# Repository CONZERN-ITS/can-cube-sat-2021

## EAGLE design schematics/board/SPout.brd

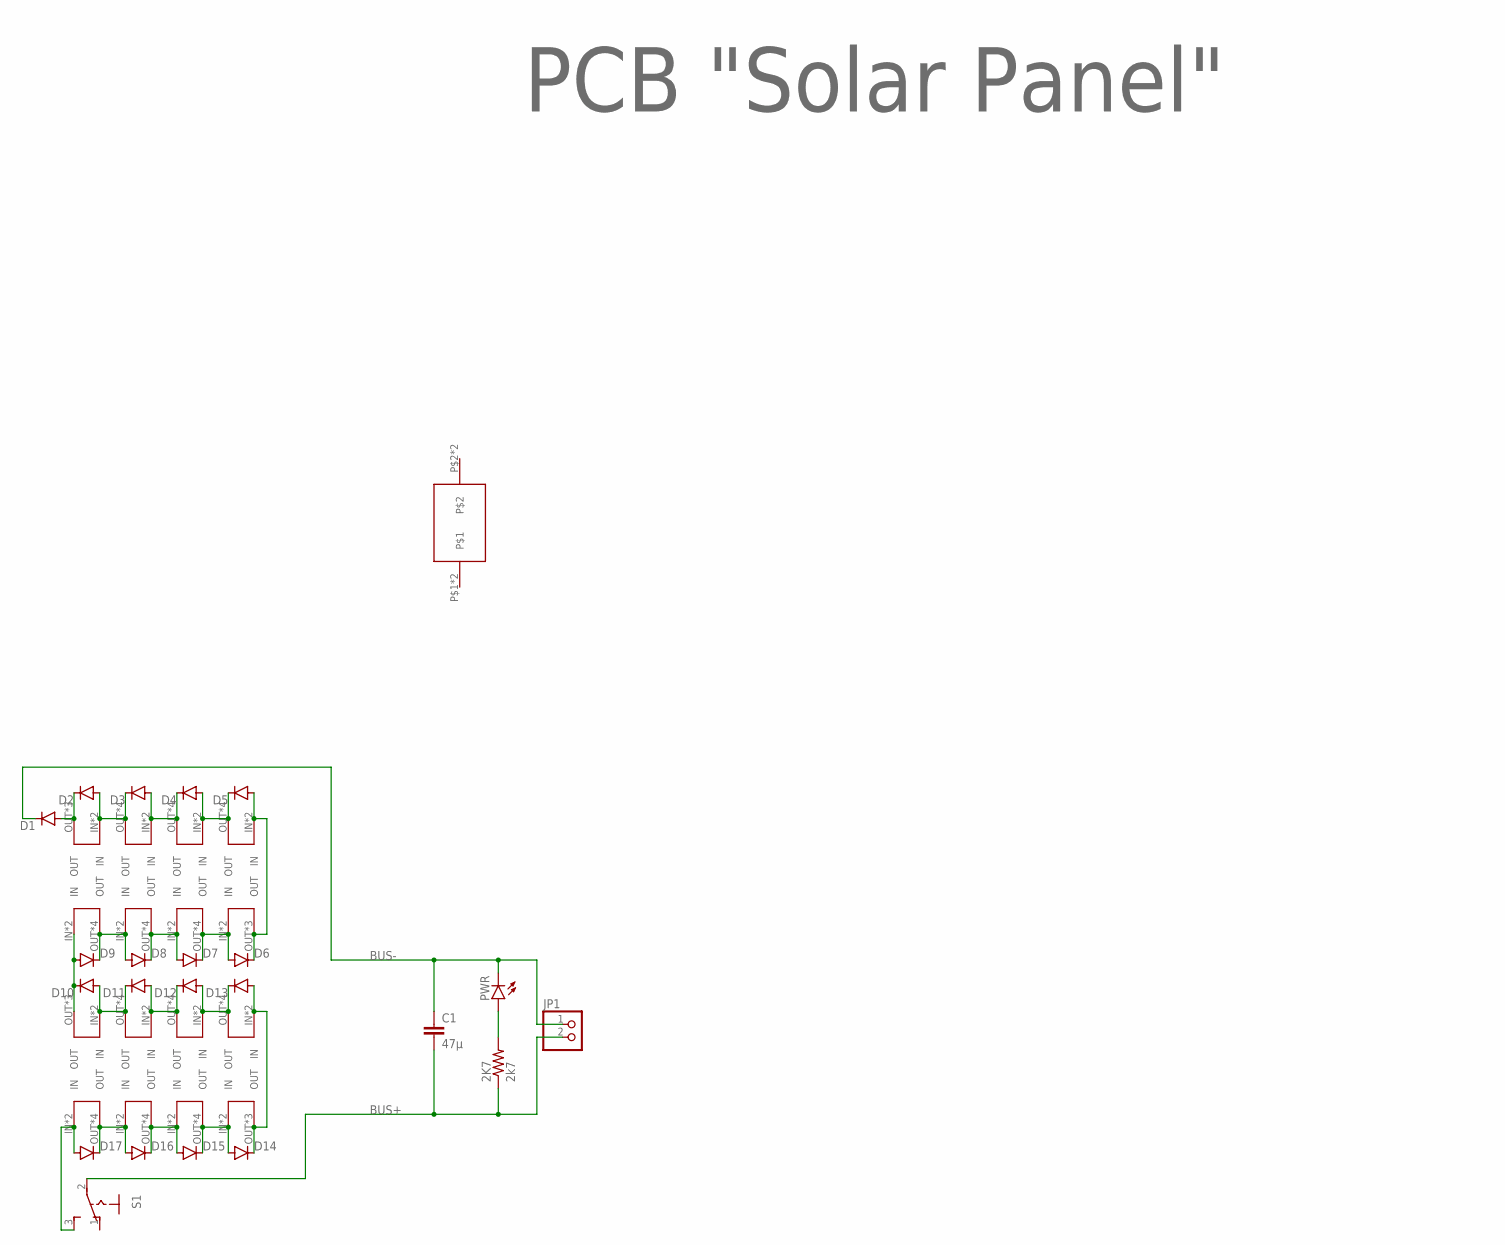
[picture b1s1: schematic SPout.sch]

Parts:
2K7: 2k7; R0603
C1: 47µ; C1210
D1, D2, D3, D4, D5, D6, D7, D8, D9, D10, D11, D12, D13, D14, D15, D16, D17: MBR0520LT; SOD123
JP1: PINHD-1X2; 1X02
PWR: LEDCHIPLED_0603; CHIPLED_0603
S1: 255SB
SOL1, SOL2, SOL3, SOL5, SOL6, SOL7, SOL9, SOL10, SOL11, SOL13, SOL14, SOL15: SOLAR-2_0; SOLAR_0-2
SOL4, SOL8, SOL12, SOL16: SOLAR-2_1; SOLAR_1-2
U$6: GRAFITGRAFIT4_2; GRAFIT4_2
U$26: PCB "Solar Panel"; ITS-LOGO

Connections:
BUS+: 2K7.1, C1.2, JP1.2, S1.2
BUS-: C1.1, D1.C, JP1.1, PWR.C
unnamed: D16.A, D17.C, SOL1.OUT, SOL1.OUT1 (OUT), SOL1.OUT-2 (OUT), SOL1.OUT-21 (OUT), SOL2.IN, SOL2.IN-2 (IN)
unnamed: D15.A, D16.C, SOL2.OUT, SOL2.OUT1 (OUT), SOL2.OUT-2 (OUT), SOL2.OUT-21 (OUT), SOL3.IN, SOL3.IN-2 (IN)
unnamed: D1.A, D2.C, SOL16.OUT, SOL16.OUT-2 (OUT), SOL16.OUT-21 (OUT)
unnamed: 2K7.2, PWR.A
unnamed: D14.A, D15.C, SOL3.OUT, SOL3.OUT1 (OUT), SOL3.OUT-2 (OUT), SOL3.OUT-21 (OUT), SOL4.IN, SOL4.IN-2 (IN)
unnamed: D17.A, S1.3 (S), SOL1.IN, SOL1.IN-2 (IN)
unnamed: D12.A, D13.C, SOL5.OUT, SOL5.OUT1 (OUT), SOL5.OUT-2 (OUT), SOL5.OUT-21 (OUT), SOL6.IN, SOL6.IN-2 (IN)
unnamed: D11.A, D12.C, SOL6.OUT, SOL6.OUT1 (OUT), SOL6.OUT-2 (OUT), SOL6.OUT-21 (OUT), SOL7.IN, SOL7.IN-2 (IN)
unnamed: D10.A, D11.C, SOL7.OUT, SOL7.OUT1 (OUT), SOL7.OUT-2 (OUT), SOL7.OUT-21 (OUT), SOL8.IN, SOL8.IN-2 (IN)
unnamed: D9.A, D10.C, SOL8.OUT, SOL8.OUT-2 (OUT), SOL8.OUT-21 (OUT), SOL9.IN, SOL9.IN-2 (IN)
unnamed: D8.A, D9.C, SOL9.OUT, SOL9.OUT1 (OUT), SOL9.OUT-2 (OUT), SOL9.OUT-21 (OUT), SOL10.IN, SOL10.IN-2 (IN)
unnamed: D7.A, D8.C, SOL10.OUT, SOL10.OUT1 (OUT), SOL10.OUT-2 (OUT), SOL10.OUT-21 (OUT), SOL11.IN, SOL11.IN-2 (IN)
unnamed: D6.A, D7.C, SOL11.OUT, SOL11.OUT1 (OUT), SOL11.OUT-2 (OUT), SOL11.OUT-21 (OUT), SOL12.IN, SOL12.IN-2 (IN)
unnamed: D5.A, D6.C, SOL12.OUT, SOL12.OUT-2 (OUT), SOL12.OUT-21 (OUT), SOL13.IN, SOL13.IN-2 (IN)
unnamed: D4.A, D5.C, SOL13.OUT, SOL13.OUT1 (OUT), SOL13.OUT-2 (OUT), SOL13.OUT-21 (OUT), SOL14.IN, SOL14.IN-2 (IN)
unnamed: D3.A, D4.C, SOL14.OUT, SOL14.OUT1 (OUT), SOL14.OUT-2 (OUT), SOL14.OUT-21 (OUT), SOL15.IN, SOL15.IN-2 (IN)
unnamed: D2.A, D3.C, SOL15.OUT, SOL15.OUT1 (OUT), SOL15.OUT-2 (OUT), SOL15.OUT-21 (OUT), SOL16.IN, SOL16.IN-2 (IN)
unnamed: D13.A, D14.C, SOL4.OUT, SOL4.OUT-2 (OUT), SOL4.OUT-21 (OUT), SOL5.IN, SOL5.IN-2 (IN)

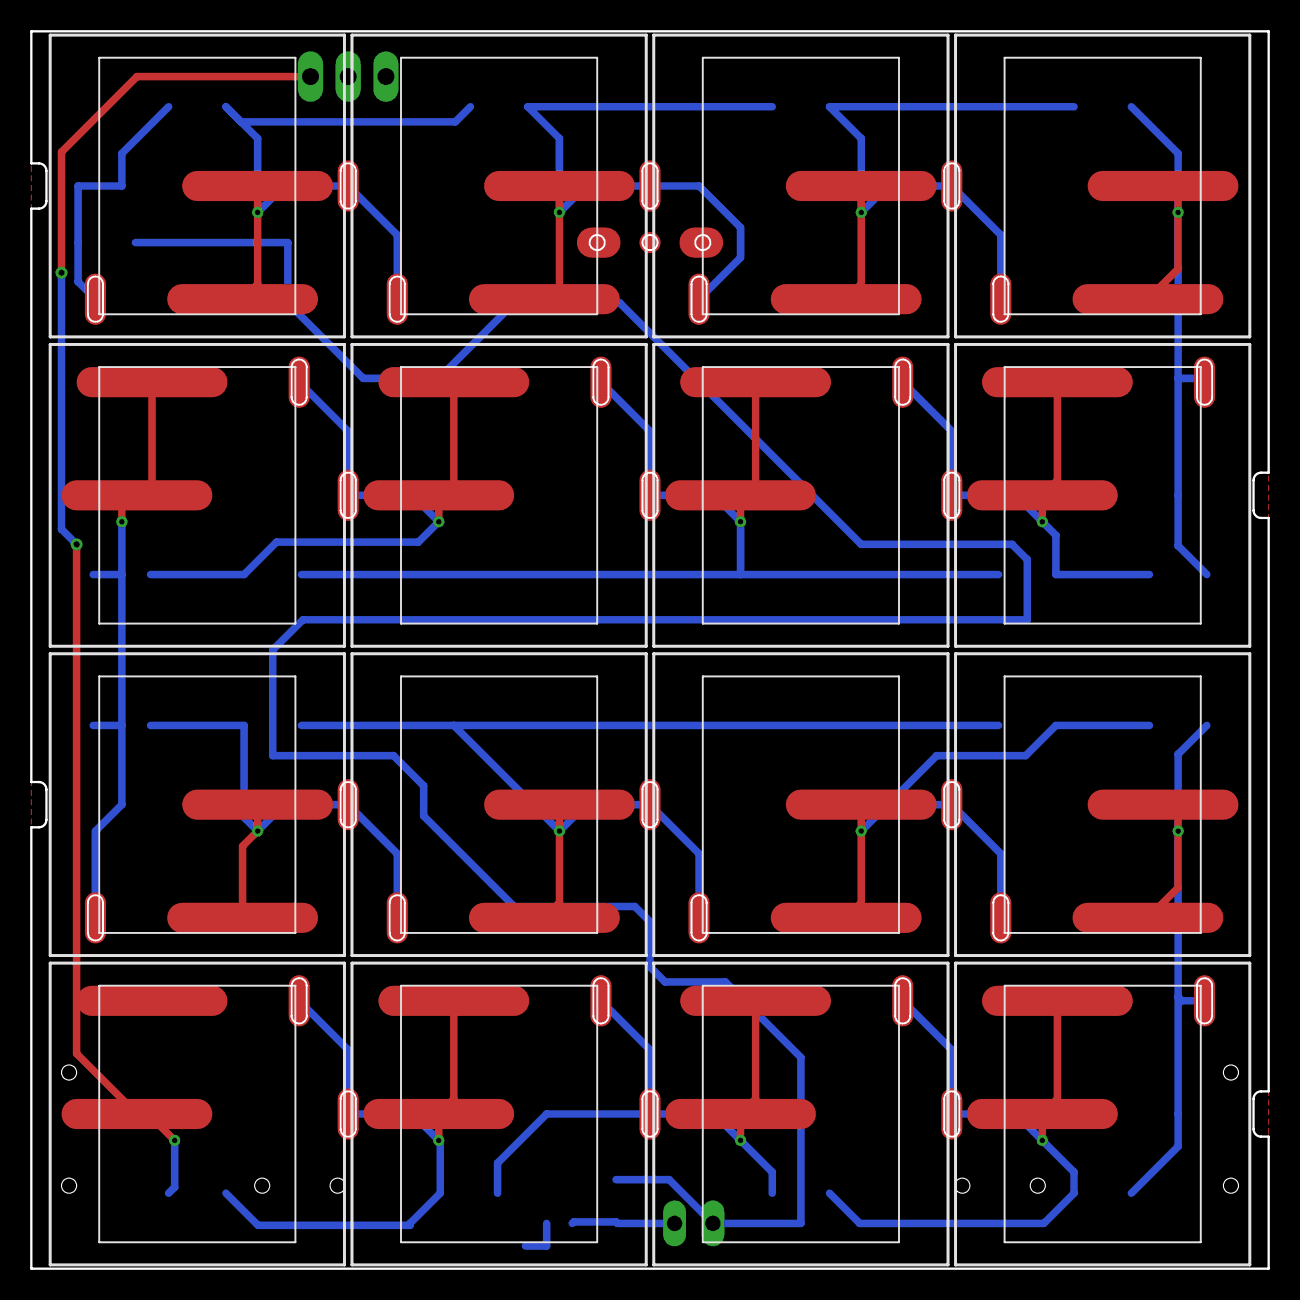
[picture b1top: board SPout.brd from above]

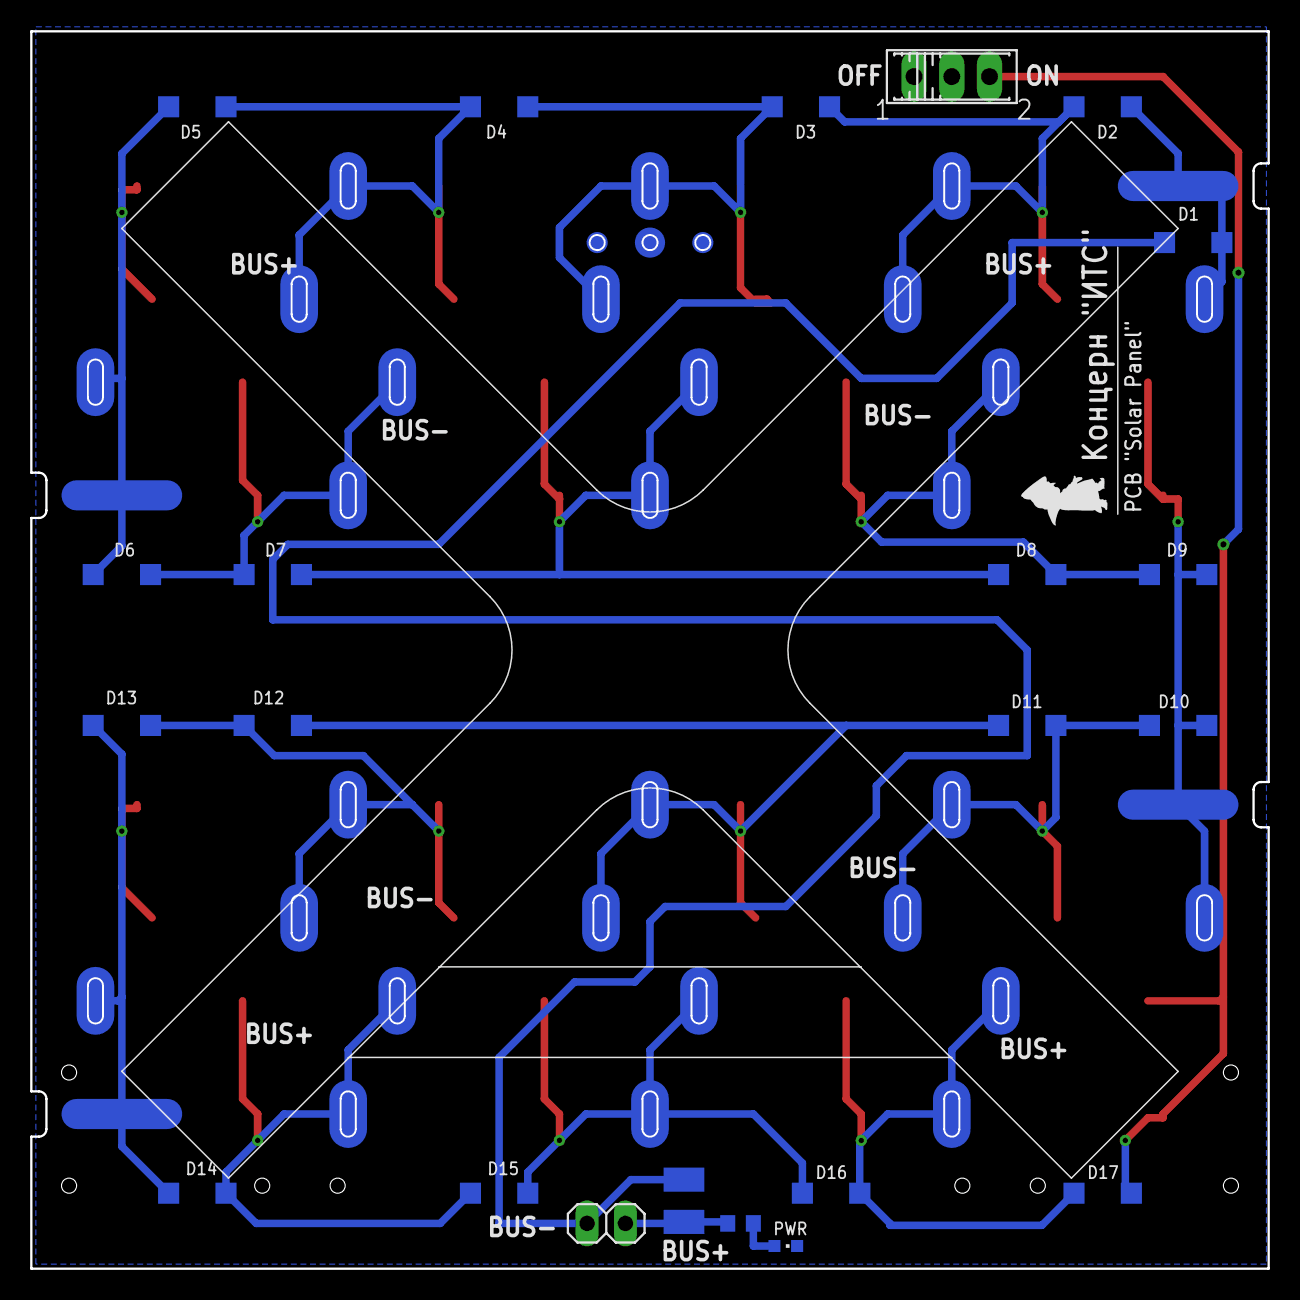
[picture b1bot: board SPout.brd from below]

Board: 2 copper layers, 82.0 x 82.0 mm, 40 parts (23 on the bottom side), 20 nets.

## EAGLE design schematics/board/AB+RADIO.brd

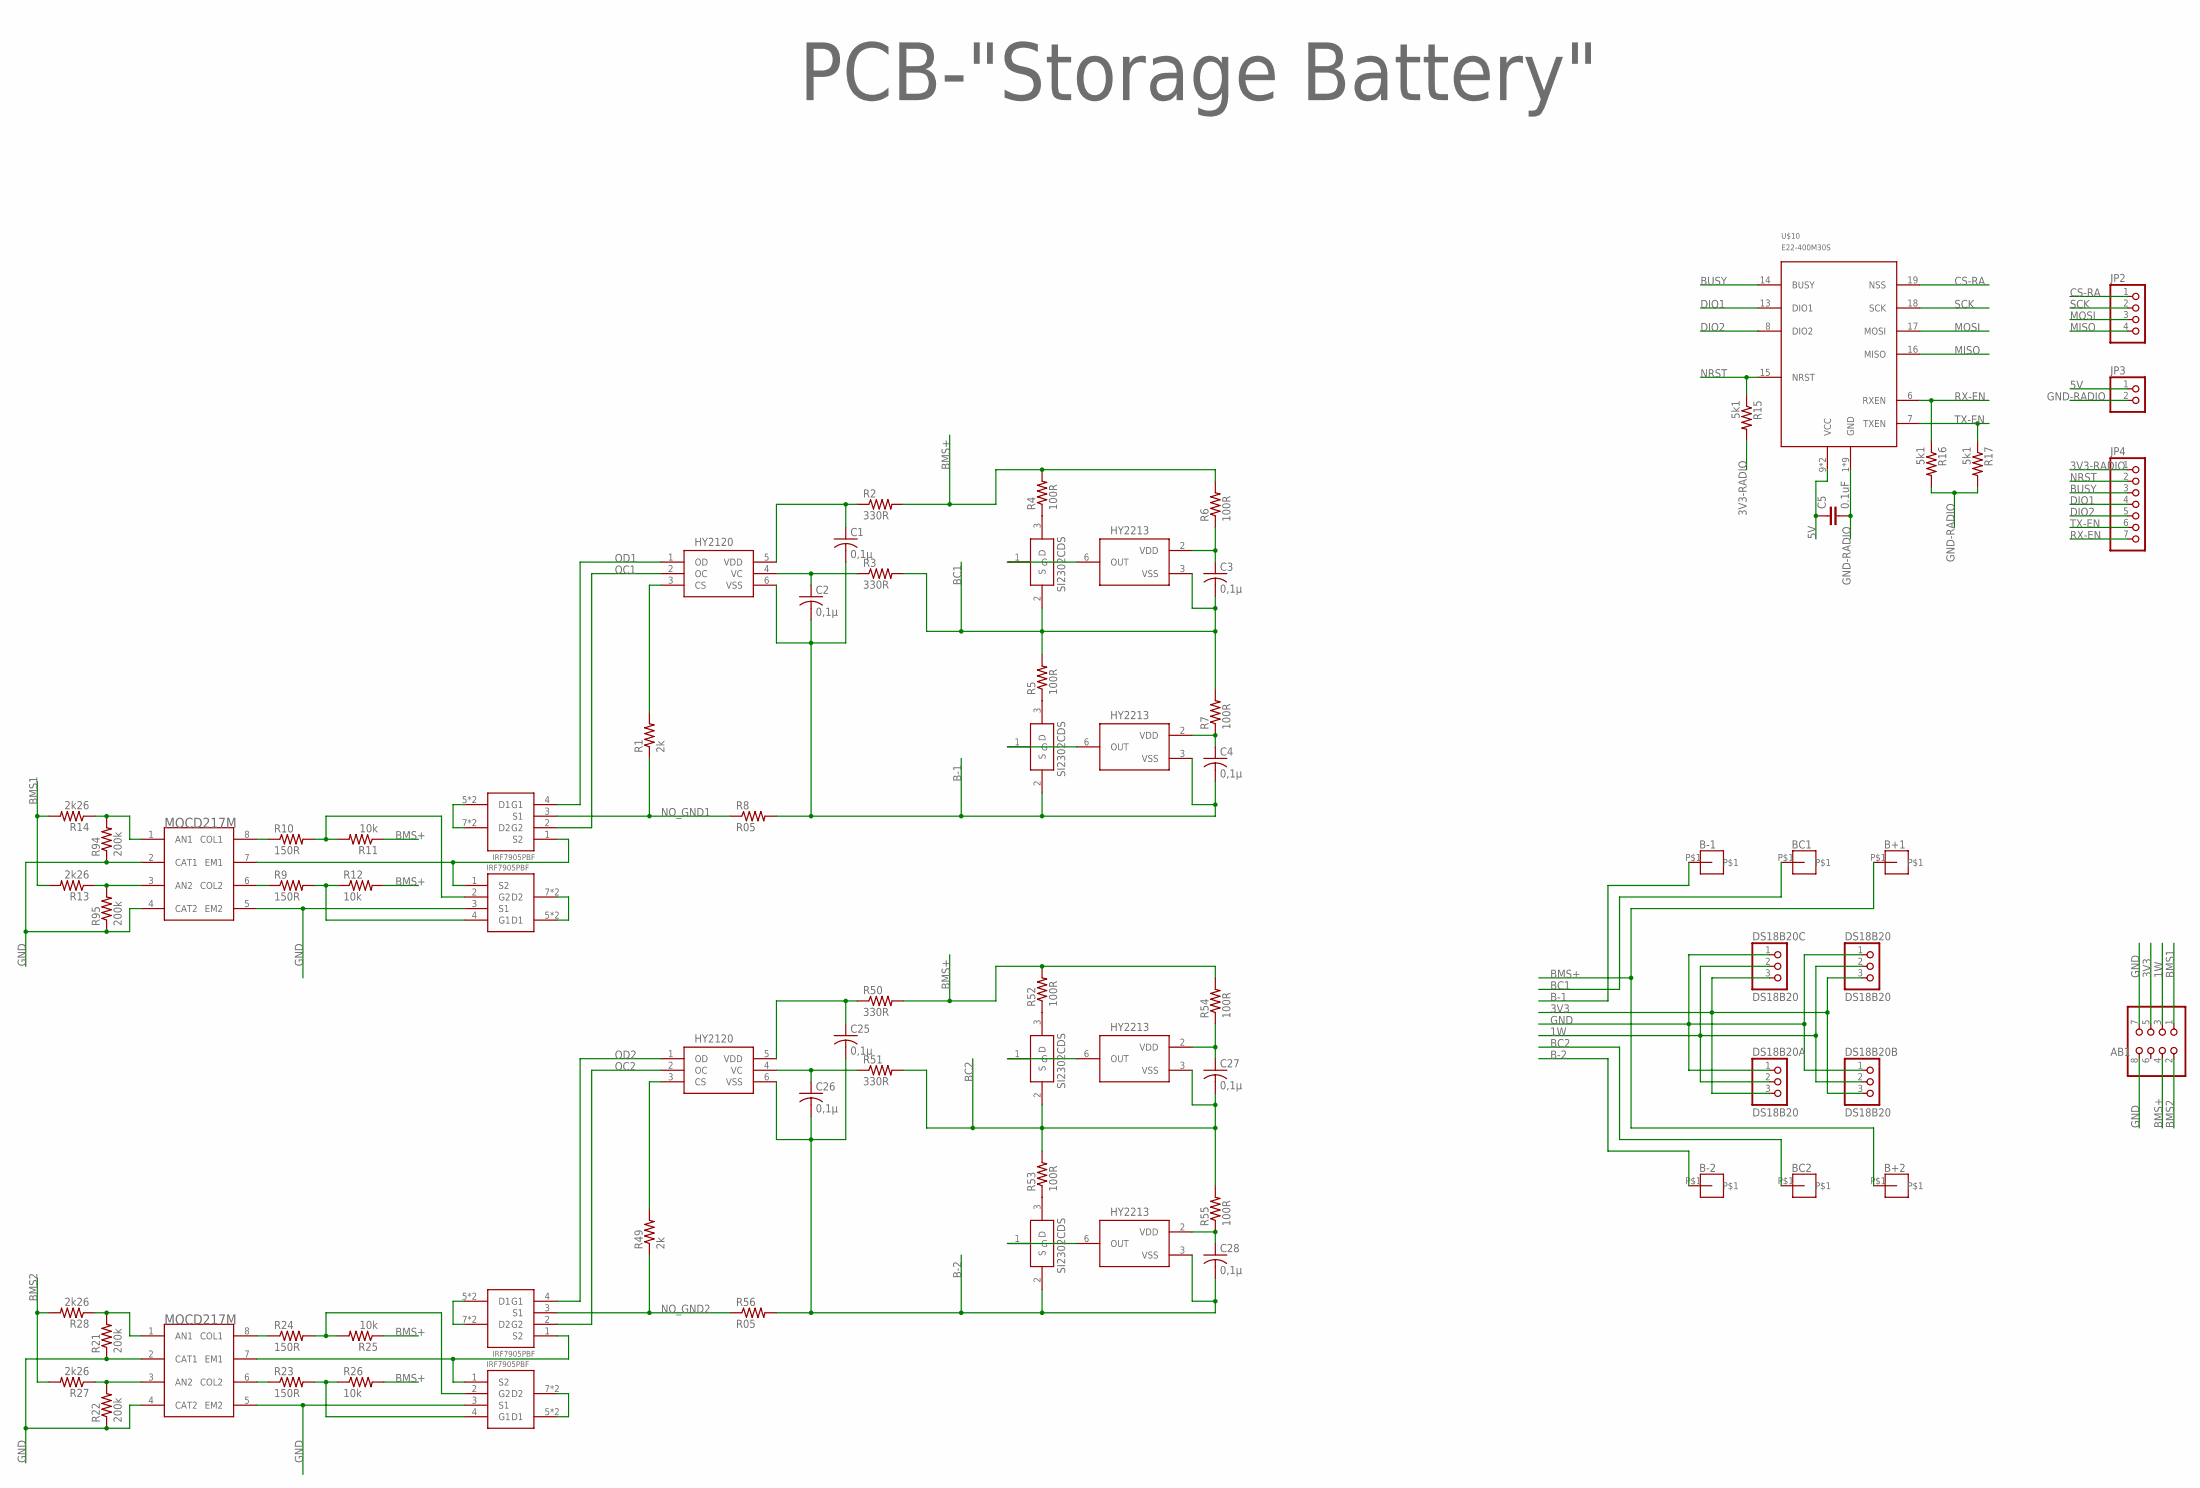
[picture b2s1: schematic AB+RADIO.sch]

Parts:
AB1: PINHD-2X4; 2X04
B+1, B+2: BATTERY
B-1, B-2: BATTERY
BC1, BC2: BATTERY
C1, C2, C3, C4, C25, C26, C27, C28: 0,1µ; C0603
C5: 0.1uF; C0603
DS18B20, DS18B20A, DS18B20B, DS18B20C: DS18B20; CONNECT1X3
JP2: PINHD-1X4; 1X04
JP3: PINHD-1X2; 1X02
JP4: PINHD-1X7; 1X07
R1, R49: 2k; R0603
R2, R3, R50, R51: 330R; R0603
R4, R5, R6, R7, R52, R53, R54, R55: 100R; R0603
R8, R56: R05; R2512
R9, R10, R23, R24: 150R; R0603
R11, R12, R25, R26: 10k; R0603
R13, R14, R27, R28: 2k26; R0603
R15, R16, R17: 5k1; R0603
R21, R22, R94, R95: 200k; R0603
U$1: PCB-"Storage Battery"; ITS-LOGO
U$2, U$11: MOCD217M; SOIC8
U$3, U$45: HY2120; SOT23-6
U$4, U$5, U$46, U$47: HY2213"; SOT23-6
U$6, U$7, U$48, U$49: SI2302CDS; SOT23-3
U$8, U$9, U$12, U$13: IRF7905PBF; SO8
U$10: E22-400M30S

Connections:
1W: AB1.3, DS18B20.2, DS18B20A.2, DS18B20B.2, DS18B20C.2
3V3: AB1.5, DS18B20.3, DS18B20A.3, DS18B20B.3, DS18B20C.3
3V3-RADIO: JP4.1, R15.2
5V: C5.1, JP3.1, U$10.9 (VCC), U$10.10 (VCC)
B-1: B-1.P$1, C1.2, C2.2, C4.2, R8.2, U$3.6 (VSS), U$5.3 (VSS), U$7.2 (S)
B-2: B-2.P$1, C25.2, C26.2, C28.2, R56.2, U$45.6 (VSS), U$47.3 (VSS), U$49.2 (S)
BC1: BC1.P$1, C3.2, R3.2, R5.2, R7.2, U$4.3 (VSS), U$6.2 (S)
BC2: BC2.P$1, C27.2, R51.2, R53.2, R55.2, U$46.3 (VSS), U$48.2 (S)
BMS1: AB1.1, R13.2, R14.2
BMS2: AB1.2, R27.2, R28.2
BMS+: AB1.4, B+1.P$1, B+2.P$1, R2.2, R4.2, R6.2, R11.1, R12.2, R25.1, R26.2, R50.2, R52.2, R54.2
BUSY: JP4.3, U$10.14 (BUSY)
CS-RA: JP2.1, U$10.19 (NSS)
DIO1: JP4.4, U$10.13 (DIO1)
DIO2: JP4.5, U$10.8 (DIO2)
GND: AB1.7, AB1.8, DS18B20.1, DS18B20A.1, DS18B20B.1, DS18B20C.1, R21.1, R22.1, R94.1, R95.1, U$2.2 (CAT1), U$2.4 (CAT2), U$2.5 (EM2), U$8.3 (S1), U$11.2 (CAT1), U$11.4 (CAT2), U$11.5 (EM2), U$12.3 (S1)
GND-RADIO: C5.2, JP3.2, R16.2, R17.2, U$10.1 (GND), U$10.2 (GND), U$10.3 (GND), U$10.4 (GND), U$10.5 (GND), U$10.11 (GND), U$10.12 (GND), U$10.20 (GND), U$10.22 (GND)
MISO: JP2.4, U$10.16 (MISO)
MOSI: JP2.3, U$10.17 (MOSI)
unnamed: U$2.7 (EM1), U$8.1 (S2), U$9.1 (S2)
unnamed: R10.2, R11.2, U$8.2 (G2)
unnamed: R49.2, U$45.3 (CS)
unnamed: C1.1, R2.1, U$3.5 (VDD)
unnamed: C3.1, R6.1, U$4.2 (VDD)
unnamed: U$4.6 (OUT), U$6.1 (G)
unnamed: C4.1, R7.1, U$5.2 (VDD)
unnamed: U$5.6 (OUT), U$7.1 (G)
unnamed: R4.1, U$6.3 (D)
unnamed: R5.1, U$7.3 (D)
unnamed: R1.2, U$3.3 (CS)
unnamed: C2.1, R3.1, U$3.4 (VC)
unnamed: U$9.5 (D1), U$9.6 (D1), U$9.7 (D2), U$9.8 (D2)
unnamed: R10.1, U$2.8 (COL1)
unnamed: R13.1, R95.2, U$2.3 (AN2)
unnamed: R22.2, R27.1, U$11.3 (AN2)
unnamed: U$8.5 (D1), U$8.6 (D1), U$8.7 (D2), U$8.8 (D2)
unnamed: R9.1, U$2.6 (COL2)
unnamed: R9.2, R12.1, U$8.4 (G1)
unnamed: R21.2, R28.1, U$11.1 (AN1)
unnamed: R14.1, R94.2, U$2.1 (AN1)
unnamed: R24.2, R25.2, U$12.2 (G2)
unnamed: R24.1, U$11.8 (COL1)
unnamed: R23.1, U$11.6 (COL2)
unnamed: R23.2, R26.1, U$12.4 (G1)
unnamed: U$11.7 (EM1), U$12.1 (S2), U$13.1 (S2)
unnamed: U$13.5 (D1), U$13.6 (D1), U$13.7 (D2), U$13.8 (D2)
unnamed: U$12.5 (D1), U$12.6 (D1), U$12.7 (D2), U$12.8 (D2)
unnamed: R52.1, U$48.3 (D)
unnamed: R53.1, U$49.3 (D)
unnamed: C25.1, R50.1, U$45.5 (VDD)
unnamed: C27.1, R54.1, U$46.2 (VDD)
unnamed: U$46.6 (OUT), U$48.1 (G)
unnamed: U$47.6 (OUT), U$49.1 (G)
unnamed: C26.1, R51.1, U$45.4 (VC)
unnamed: C28.1, R55.1, U$47.2 (VDD)
NO_GND1: R1.1, R8.1, U$9.3 (S1)
NO_GND2: R49.1, R56.1, U$13.3 (S1)
NRST: JP4.2, R15.1, U$10.15 (NRST)
OC1: U$3.2 (OC), U$9.2 (G2)
OC2: U$13.2 (G2), U$45.2 (OC)
OD1: U$3.1 (OD), U$9.4 (G1)
OD2: U$13.4 (G1), U$45.1 (OD)
RX-EN: JP4.7, R16.1, U$10.6 (RXEN)
SCK: JP2.2, U$10.18 (SCK)
TX-EN: JP4.6, R17.1, U$10.7 (TXEN)

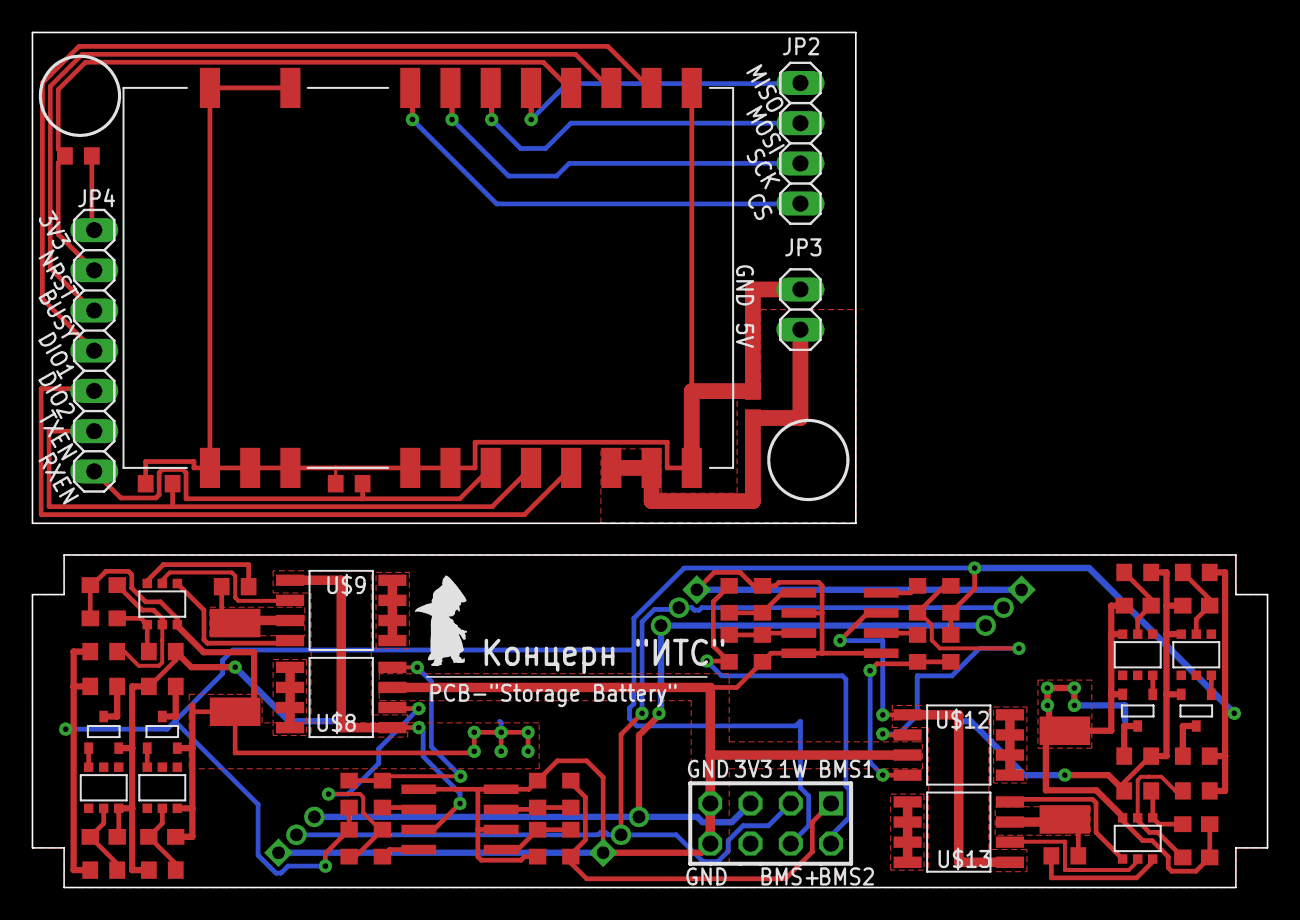
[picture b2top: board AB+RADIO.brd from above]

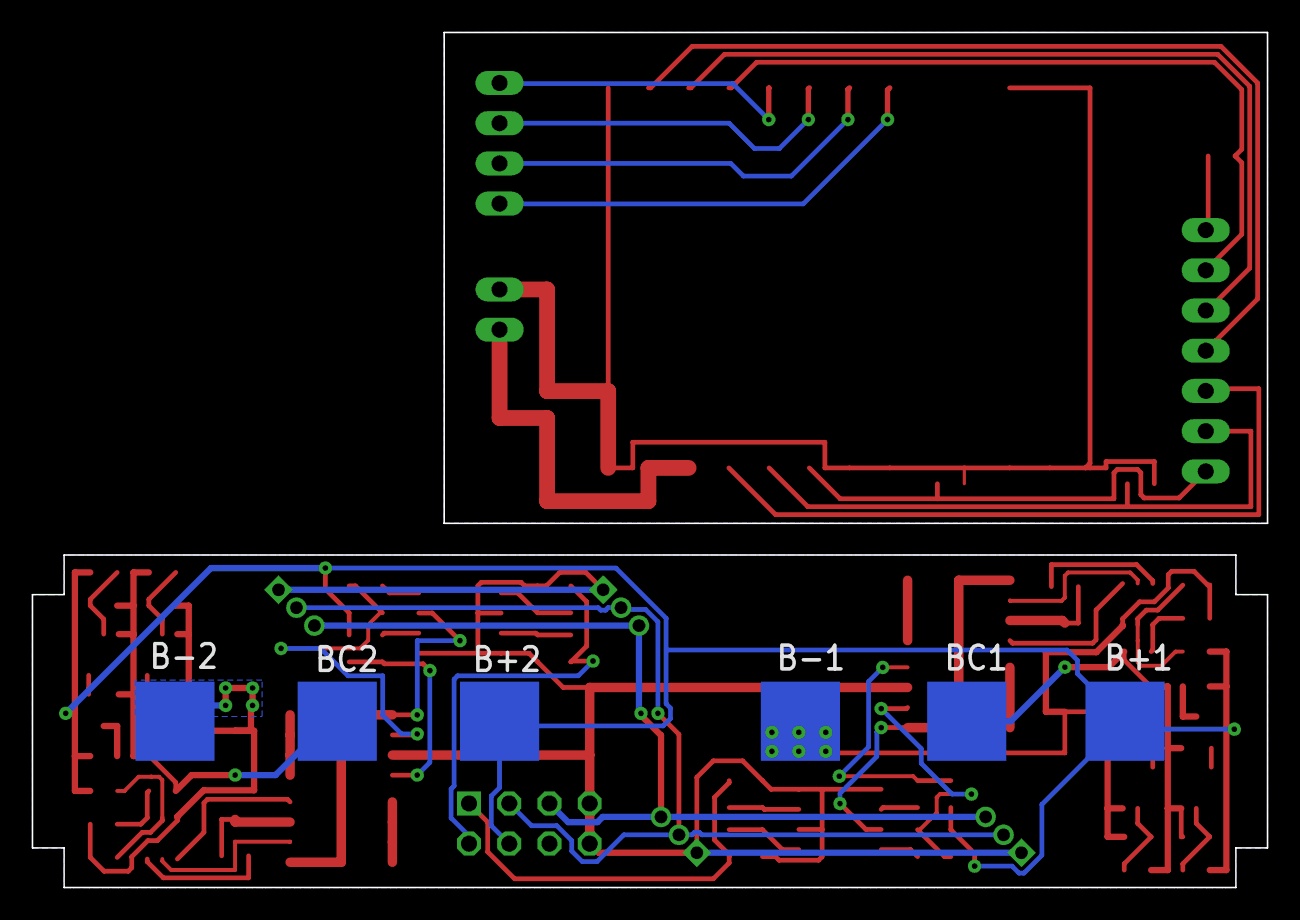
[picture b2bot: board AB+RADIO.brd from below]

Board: 2 copper layers, 78.0 x 54.0 mm, 76 parts (6 on the bottom side), 65 nets.

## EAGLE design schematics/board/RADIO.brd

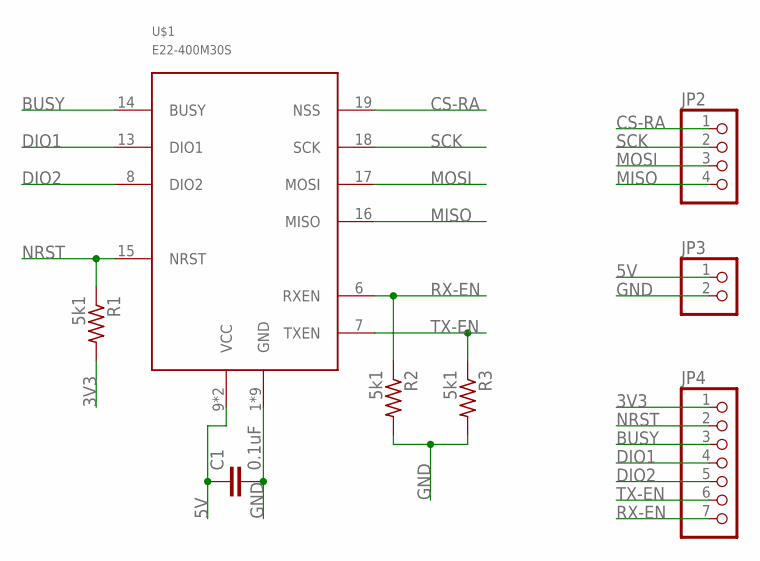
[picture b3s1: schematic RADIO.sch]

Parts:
C1: 0.1uF; C0603
JP2: PINHD-1X4; 1X04
JP3: PINHD-1X2; 1X02
JP4: PINHD-1X7; 1X07
R1, R2, R3: 5k1; R0603
U$1: E22-400M30S

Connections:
3V3: JP4.1, R1.2
5V: C1.1, JP3.1, U$1.9 (VCC), U$1.10 (VCC)
BUSY: JP4.3, U$1.14 (BUSY)
CS-RA: JP2.1, U$1.19 (NSS)
DIO1: JP4.4, U$1.13 (DIO1)
DIO2: JP4.5, U$1.8 (DIO2)
GND: C1.2, JP3.2, R2.2, R3.2, U$1.1 (GND), U$1.2 (GND), U$1.3 (GND), U$1.4 (GND), U$1.5 (GND), U$1.11 (GND), U$1.12 (GND), U$1.20 (GND), U$1.22 (GND)
MISO: JP2.4, U$1.16 (MISO)
MOSI: JP2.3, U$1.17 (MOSI)
NRST: JP4.2, R1.1, U$1.15 (NRST)
RX-EN: JP4.7, R2.1, U$1.6 (RXEN)
SCK: JP2.2, U$1.18 (SCK)
TX-EN: JP4.6, R3.1, U$1.7 (TXEN)

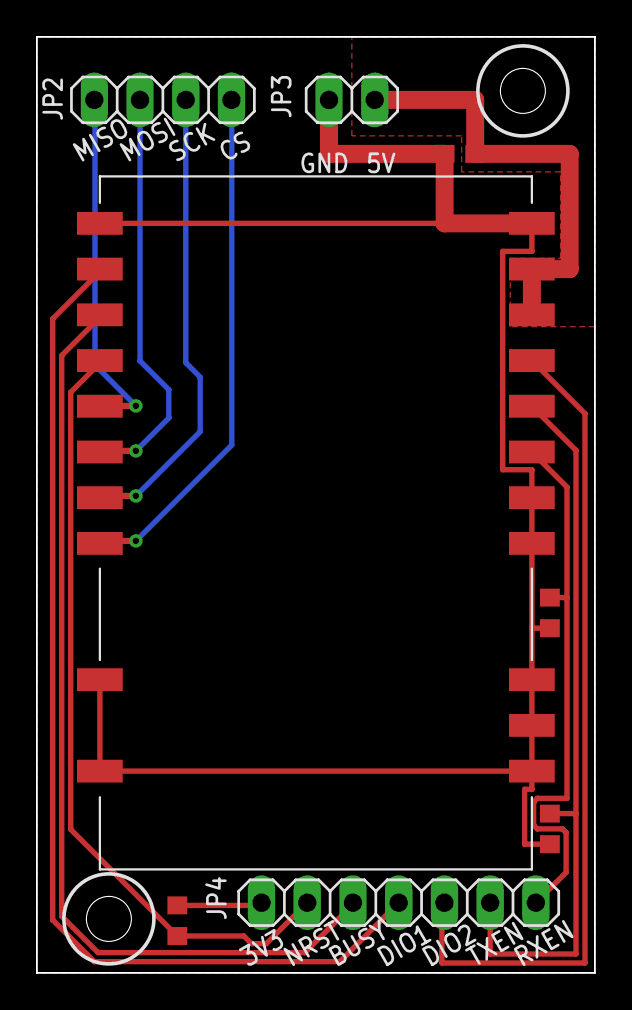
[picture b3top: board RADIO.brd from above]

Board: 2 copper layers, 31.0 x 52.0 mm, 8 parts (0 on the bottom side), 13 nets.

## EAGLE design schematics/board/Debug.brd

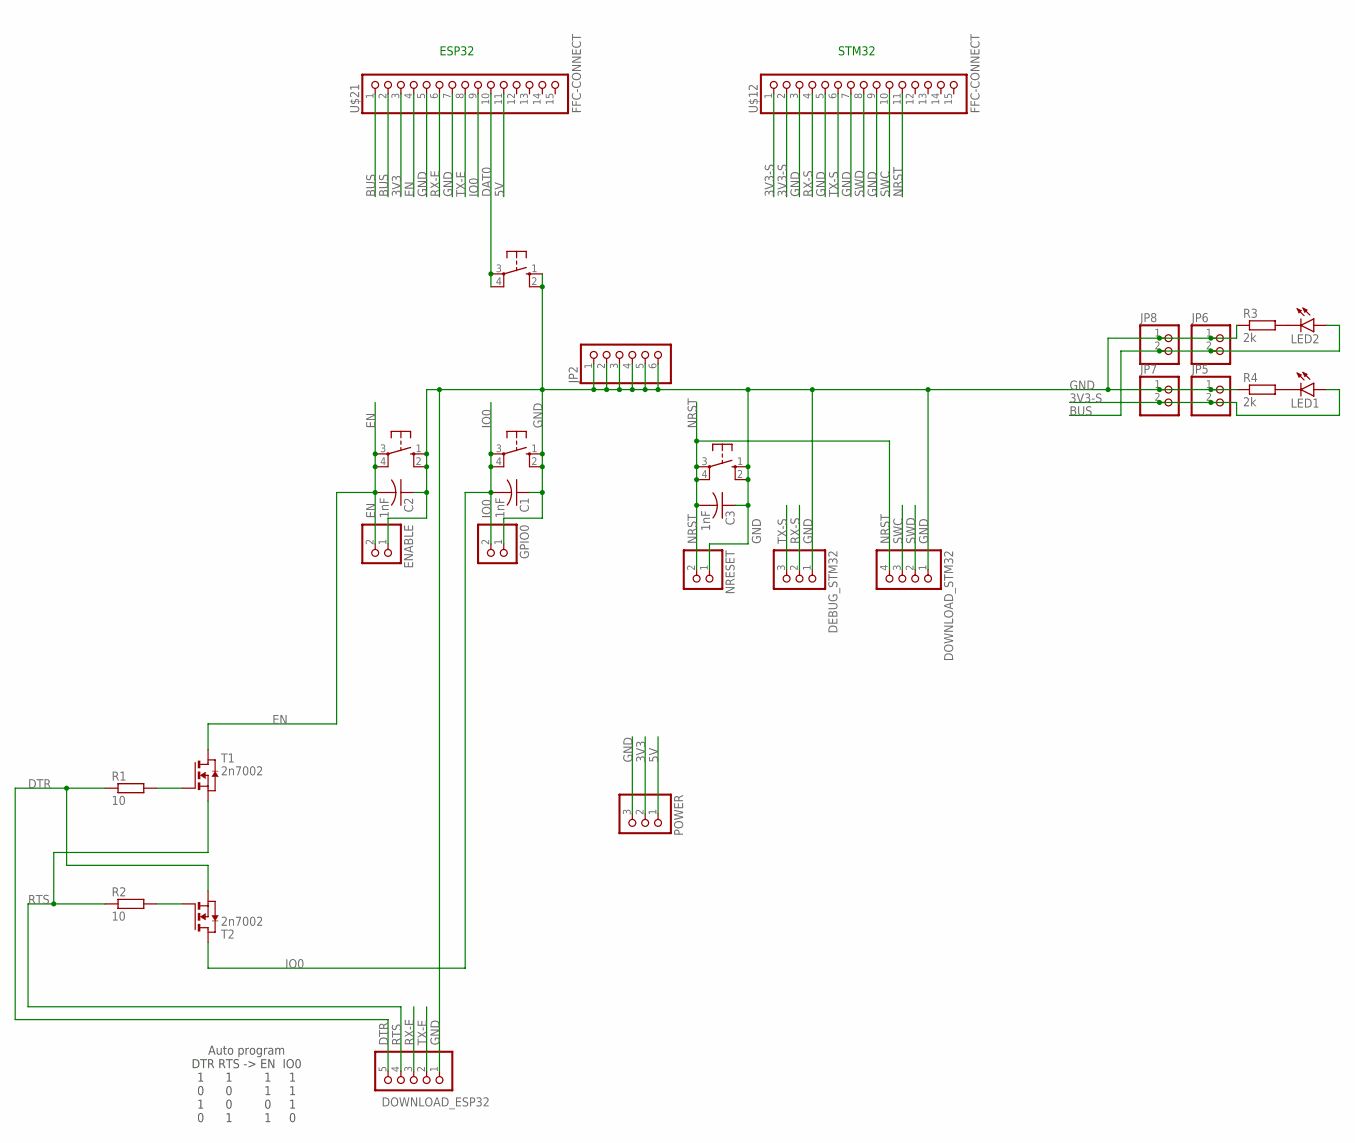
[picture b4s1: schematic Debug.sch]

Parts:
C1, C2, C3: 1nF; C0603
DAT0: 10-XX; B3F-10XX
DEBUG_STM32: PINHD-1X3; 1X03
DOWNLOAD_ESP32: PINHD-1X5; 1X05
DOWNLOAD_STM32: PINHD-1X4; 1X04
EN: 10-XX; B3F-10XX
ENABLE: PINHD-1X2; 1X02
GPIO0: PINHD-1X2; 1X02
IO0: 10-XX; B3F-10XX
JP2: PINHD-1X6; 1X06
JP5, JP6, JP7, JP8: PINHD-1X2; 1X02
LED1, LED2: LEDCHIPLED_0603; CHIPLED_0603
NRESET: PINHD-1X2; 1X02
NRST: 10-XX; B3F-10XX
POWER: PINHD-1X3; 1X03
R1, R2: 10; R0603
R3, R4: 2k; R0603
T1, T2: 2n7002; SOT-23
U$12, U$21: FFC-CONNECT; SLW15S

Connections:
3V3: POWER.2, U$21.3
3V3-S: JP5.2, JP7.2, LED1.A, U$12.1, U$12.2
5V: POWER.1, U$21.11
BUS: JP6.2, JP8.2, LED2.A, U$21.1, U$21.2
DAT0: DAT0.3, DAT0.4 (P1), U$21.10
DTR: DOWNLOAD_ESP32.5, R1.1, T2.2 (S)
EN: C2.2, EN.3, EN.4 (P1), ENABLE.2, T1.1 (D), U$21.4
GND: C1.1, C2.1, C3.1, DAT0.1 (S), DAT0.2 (S1), DEBUG_STM32.1, DOWNLOAD_ESP32.1, DOWNLOAD_STM32.1, EN.1 (S), EN.2 (S1), ENABLE.1, GPIO0.1, IO0.1 (S), IO0.2 (S1), JP2.1, JP2.2, JP2.3, JP2.4, JP2.5, JP2.6, JP5.1, JP6.1, JP7.1, JP8.1, NRESET.1, NRST.1 (S), NRST.2 (S1), POWER.3, R3.1, R4.1, U$12.3, U$12.5, U$12.7, U$12.9, U$21.5, U$21.7
IO0: C1.2, GPIO0.2, IO0.3, IO0.4 (P1), T2.1 (D), U$21.9
unnamed: R2.2, T2.3 (G)
unnamed: R1.2, T1.3 (G)
unnamed: LED1.C, R4.2
unnamed: LED2.C, R3.2
NRST: C3.2, DOWNLOAD_STM32.4, NRESET.2, NRST.3, NRST.4 (P1), U$12.11
RTS: DOWNLOAD_ESP32.4, R2.1, T1.2 (S)
RX-E: DOWNLOAD_ESP32.3, U$21.6
RX-S: DEBUG_STM32.2, U$12.4
SWC: DOWNLOAD_STM32.3, U$12.10
SWD: DOWNLOAD_STM32.2, U$12.8
TX-E: DOWNLOAD_ESP32.2, U$21.8
TX-S: DEBUG_STM32.3, U$12.6

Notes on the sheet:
ESP32
STM32
Auto program DTR RTS -> EN IO0 1 1 1 1 0 0 1 1 1 0 0 1 0 1 1 0

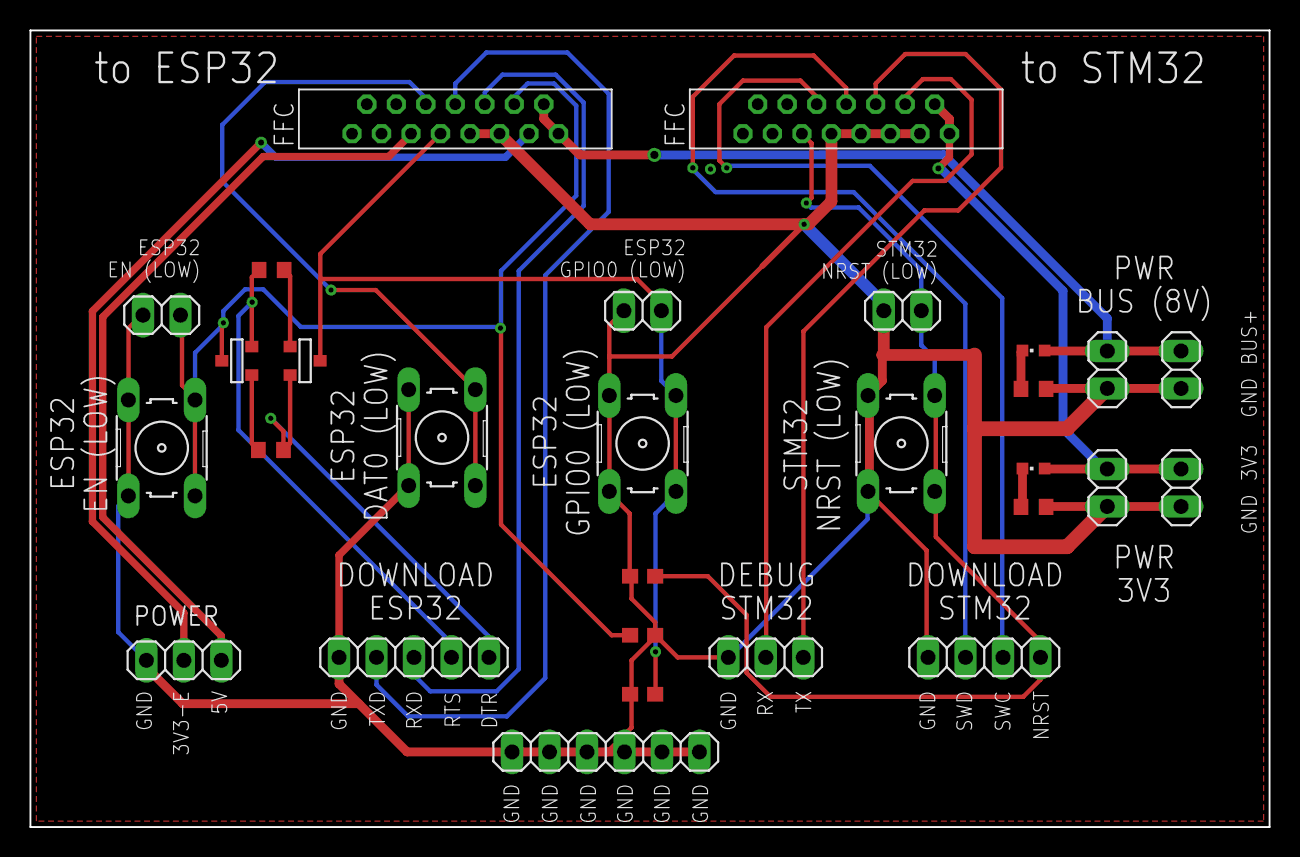
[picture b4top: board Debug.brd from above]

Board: 2 copper layers, 84.0 x 54.0 mm, 29 parts (0 on the bottom side), 21 nets.

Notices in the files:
parts and their libraries:
SparkFun-Batteries: Licensing: Creative Commons ShareAlike 4.0 International - https://creativecommons.org/licenses/by-sa/4.0
